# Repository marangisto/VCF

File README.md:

# VCF
Voltage Controlled Filter

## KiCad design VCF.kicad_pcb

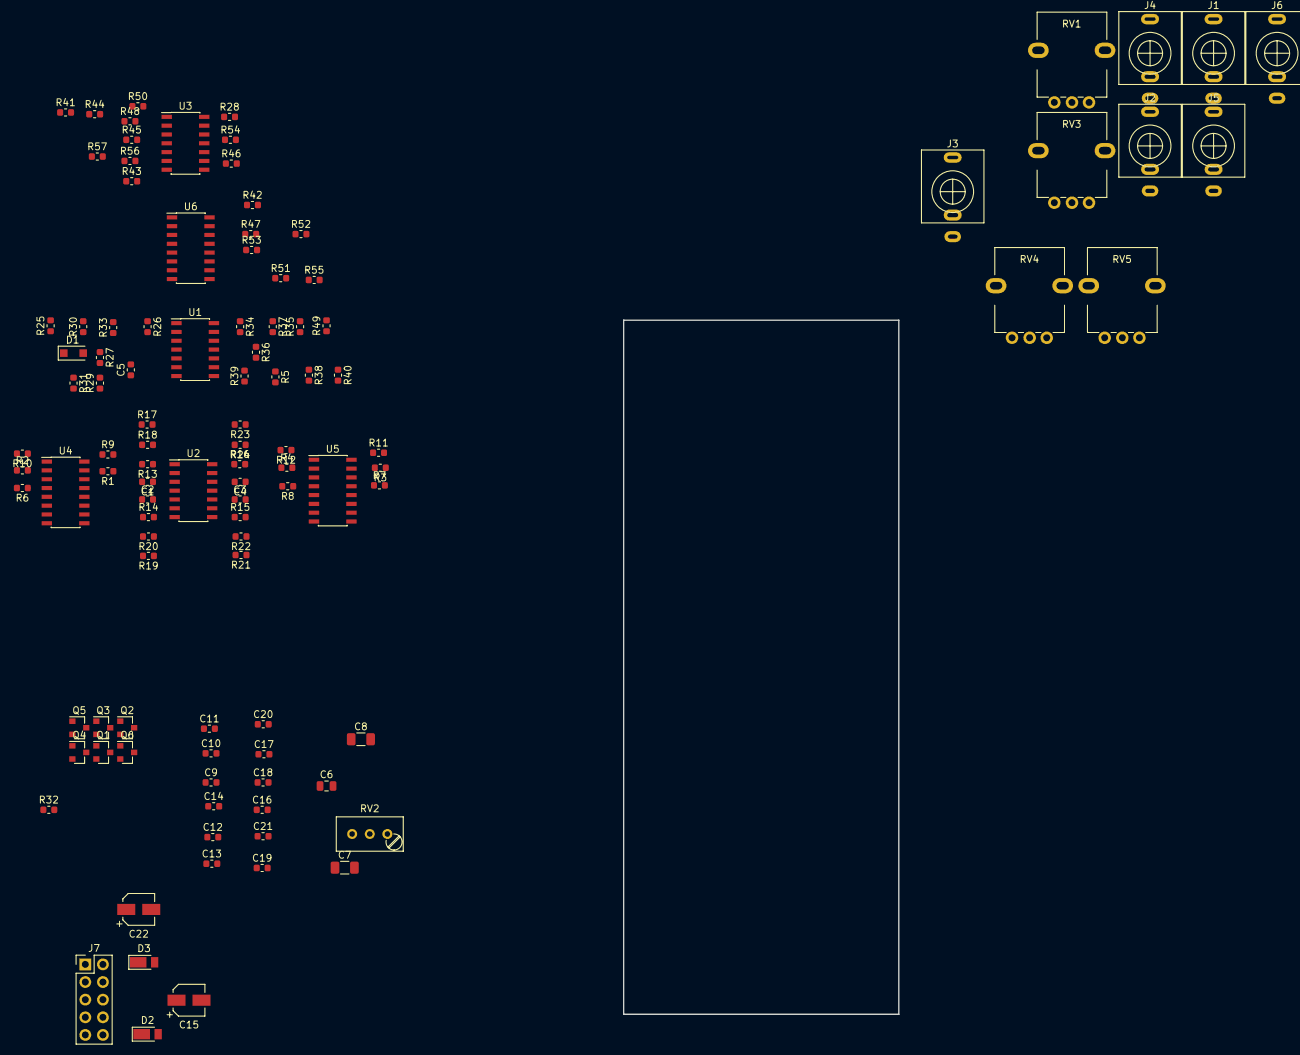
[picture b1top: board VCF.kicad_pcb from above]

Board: 2 copper layers, 106 parts (0 on the bottom side), 70 nets, no tracks yet.

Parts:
C1, C2, C3, C4, C5: 100p; C_0603_1608Metric
C6: 100n; C_0805_2012Metric
C7, C8: 470n; C_1206_3216Metric
C9, C10, C11, C12, C13, C14, C16, C17, C18, C19, C20, C21: 100n; C_0603_1608Metric
C15, C22: 10u; CP_Elec_4x5.8
D1: 1N4148; D_SOD-123F
D2, D3: DFLR1400-7; D_PowerDI-123
J1, J2, J3, J4, J5, J6: AudioJack2_Ground_Switch; PJ398SM
J7: Conn_02x05_Odd_Even; Pin_Header_Straight_2x05_Pitch2.54mm
Q1, Q2, Q3, Q4: BC857; SOT-23
Q5, Q6: BC847; SOT-23
R1, R2, R3, R4: 20k; R_0603_1608Metric
R5, R6, R7, R8, R13, R14, R15, R16, R25, R30, R33, R34, R37, R38, R40, R41, R43, R48, R50, R57: 100k; R_0603_1608Metric
R9, R10, R11, R12, R31: 10k; R_0603_1608Metric
R17, R19, R21, R23: 39k; R_0603_1608Metric
R18, R20, R22, R24: 100; R_0603_1608Metric
R26: 1k6; R_0603_1608Metric
R27: 1M; R_0603_1608Metric
R28: 75k; R_0603_1608Metric
R29: 28k; R_0603_1608Metric
R32: 470; R_0603_1608Metric
R35, R52: 1k; R_0603_1608Metric
R36: 4M7; R_0603_1608Metric
R39: 470k; R_0603_1608Metric
R42, R49, R53, R56: 30k; R_0603_1608Metric
R44, R46: 120k; R_0603_1608Metric
R45, R54: 47k; R_0603_1608Metric
R47: 200k; R_0603_1608Metric
R51: 150k; R_0603_1608Metric
R55: R; R_0603_1608Metric
RV1, RV3, RV4, RV5: 100k; AlpsRK09K
RV2: 100; Potentiometer_Trimmer_Bourns_3296W
U1, U2, U3: TL074; SOIC-14_3.9x8.7mm_Pitch1.27mm
U4, U5, U6: LM13700; SOIC-16_3.9x9.9mm_Pitch1.27mm

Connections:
+12V: C9.1, C10.1, C11.1, C12.1, C13.1, C14.1, C15.1, D2.1, R1.1, R2.1, R3.1, R4.1, R27.1, R45.1, RV1.1, U1.4, U2.4, U3.4, U4.11, U5.11, U6.11
-12V: C16.2, C17.2, C18.2, C19.2, C20.2, C21.2, C22.2, D3.2, R17.2, R19.2, R21.2, R23.2, R28.2, R54.2, R57.2, U1.11, U2.11, U3.11, U4.6, U5.6, U6.6
GND: C1.2, C2.2, C3.2, C4.2, C9.2, C10.2, C11.2, C12.2, C13.2, C14.2, C15.2, C16.1, C17.1, C18.1, C19.1, C20.1, C21.1, C22.1, J1.S, J1.TN, J2.S, J2.TN, J3.S, J4.S, J4.TN, J5.S, J5.TN, J6.S, J6.TN, J7.3, J7.4, J7.5, J7.6, J7.7, J7.8, Q1.1, Q2.1, Q3.1, Q4.1, Q6.2, R18.2, R20.2, R22.2, R24.2, R32.2, R36.2, R37.1, R52.2, R53.1, R55.2, R56.2, RV4.3, RV5.3, U1.3, U1.5, U1.10, U3.3, U3.10, U3.12, U4.3, U4.14, U5.3, U5.14, U6.3, U6.4, U6.13
unnamed: C1.1, U2.3, U4.12
unnamed: C2.1, U2.5, U4.5
unnamed: C3.1, U2.10, U5.12
unnamed: C4.1, U2.12, U5.5
unnamed: C5.1, R29.1, R31.2, U1.7
unnamed: C5.2, Q5.3, R27.2, U1.6
unnamed: C6.1, R36.1, U1.12
unnamed: C6.2, R16.1, U2.13, U2.14
unnamed: C7.1, R38.2
unnamed: C7.2, RV4.2
unnamed: C8.1, R40.2
unnamed: C8.2, RV5.2
unnamed: D1.1, R29.2
unnamed: D1.2, Q5.2, RV2.2
unnamed: D2.2, J7.9, J7.10
unnamed: D3.1, J7.1, J7.2
unnamed: J1.T, R30.2
unnamed: J2.T, R33.2
unnamed: J3.T, R35.1
unnamed: J4.T, RV4.1
unnamed: J5.T, RV5.1
unnamed: J6.T, R41.2
unnamed: Q1.2, Q2.2, Q3.2, Q4.2, Q6.3
unnamed: Q1.3, R9.2
unnamed: Q2.3, R10.2
unnamed: Q3.3, R11.2
unnamed: Q4.3, R12.2
unnamed: Q5.1, Q6.1, R31.1
unnamed: R1.2, U4.15
unnamed: R2.2, U4.2
unnamed: R3.2, U5.15
unnamed: R4.2, U5.2
unnamed: R9.1, U4.16
unnamed: R10.1, U4.1
unnamed: R11.1, U5.16
unnamed: R12.1, U5.1
unnamed: R6.2, R13.1, U2.1, U2.2
unnamed: R5.1, R13.2, R17.1, R18.1, R51.1, U4.13
unnamed: R7.2, R14.1, U2.6, U2.7
unnamed: R6.1, R14.2, R19.1, R20.1, U4.4
unnamed: R8.2, R15.1, U2.8, U2.9
unnamed: R7.1, R15.2, R21.1, R22.1, U5.13
unnamed: R8.1, R16.2, R23.1, R24.1, U5.4
unnamed: R25.1, R26.2, R30.1, R33.1, U1.2
unnamed: R25.2, RV1.2
unnamed: R26.1, RV2.1, U1.1
unnamed: R28.1, RV1.3
unnamed: R32.1, RV2.3
unnamed: R34.1, R35.2, R49.2, U1.14
unnamed: R34.2, R37.2, U1.13
unnamed: R38.1, R39.2, R40.1, U1.9
unnamed: R5.2, R39.1, U1.8
unnamed: R41.1, R44.2, R48.1, U3.2
unnamed: R42.1, U6.16
unnamed: R42.2, R43.1, U3.7
unnamed: R43.2, R50.1, U3.6
unnamed: R44.1, R50.2, U3.1
unnamed: R45.2, RV3.1
unnamed: R46.1, R47.2, U3.8
unnamed: R46.2, R49.1, U3.9
unnamed: R47.1, R52.1, U6.14
unnamed: R48.2, RV3.2
unnamed: R51.2, R55.1, U6.9
unnamed: R53.2, U6.10, U6.12
unnamed: R54.1, RV3.3
unnamed: R56.1, R57.1, U3.5
unnamed: U3.13, U3.14

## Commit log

2018-08-29 Initial circuit.
2018-08-29 Partial placement.
2018-09-14 More footprints and placement.
2018-11-12 More work on layout.
2019-05-01 More developement work.
